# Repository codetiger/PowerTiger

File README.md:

# PowerTiger

## Overview
This project is an open-source energy monitoring solution designed to track and measure power consumption in a household. The design is centered around the Raspberry Pi Pico W, interfaced with Current Transformer (CT) sensors via a custom PCB. The project is developed using KiCad for PCB design and is part of an open-source hardware (OSH) initiative.

## Features
1. Real-time power monitoring: Accurately measure and track power usage in real-time using CT sensors.
2. Wireless communication: The RPi Pico W provides wireless connectivity, enabling easy integration with IoT platforms.
3. Scalable design: Supports multiple CT sensors to monitor different circuits or devices.
4. Open-source hardware and software: The design files and source code are freely available for customization and improvement as part of the OSH initiative.

## Project Components
* Raspberry Pi Pico W: The microcontroller at the heart of the project, providing processing power and wireless connectivity.
* Custom PCB: Designed in KiCad, this PCB interfaces with the CT sensors for power measurement of various terminals.
* CT Sensors: Used to measure the current flowing through the electrical wires, providing the data needed for power calculation.
* Software: The firmware is written in CircuitPython, running on the RPi Pico W.

| | Components | Count |
|-|------------|-------|
|1| SCT-013-030 | 5 |
|2| SCT-013-015 | 5 |
|3| SCT-013-005 | 6 |

The json config support configuring 16 CT sensors in any combination as required.

## Grafana Dashboard

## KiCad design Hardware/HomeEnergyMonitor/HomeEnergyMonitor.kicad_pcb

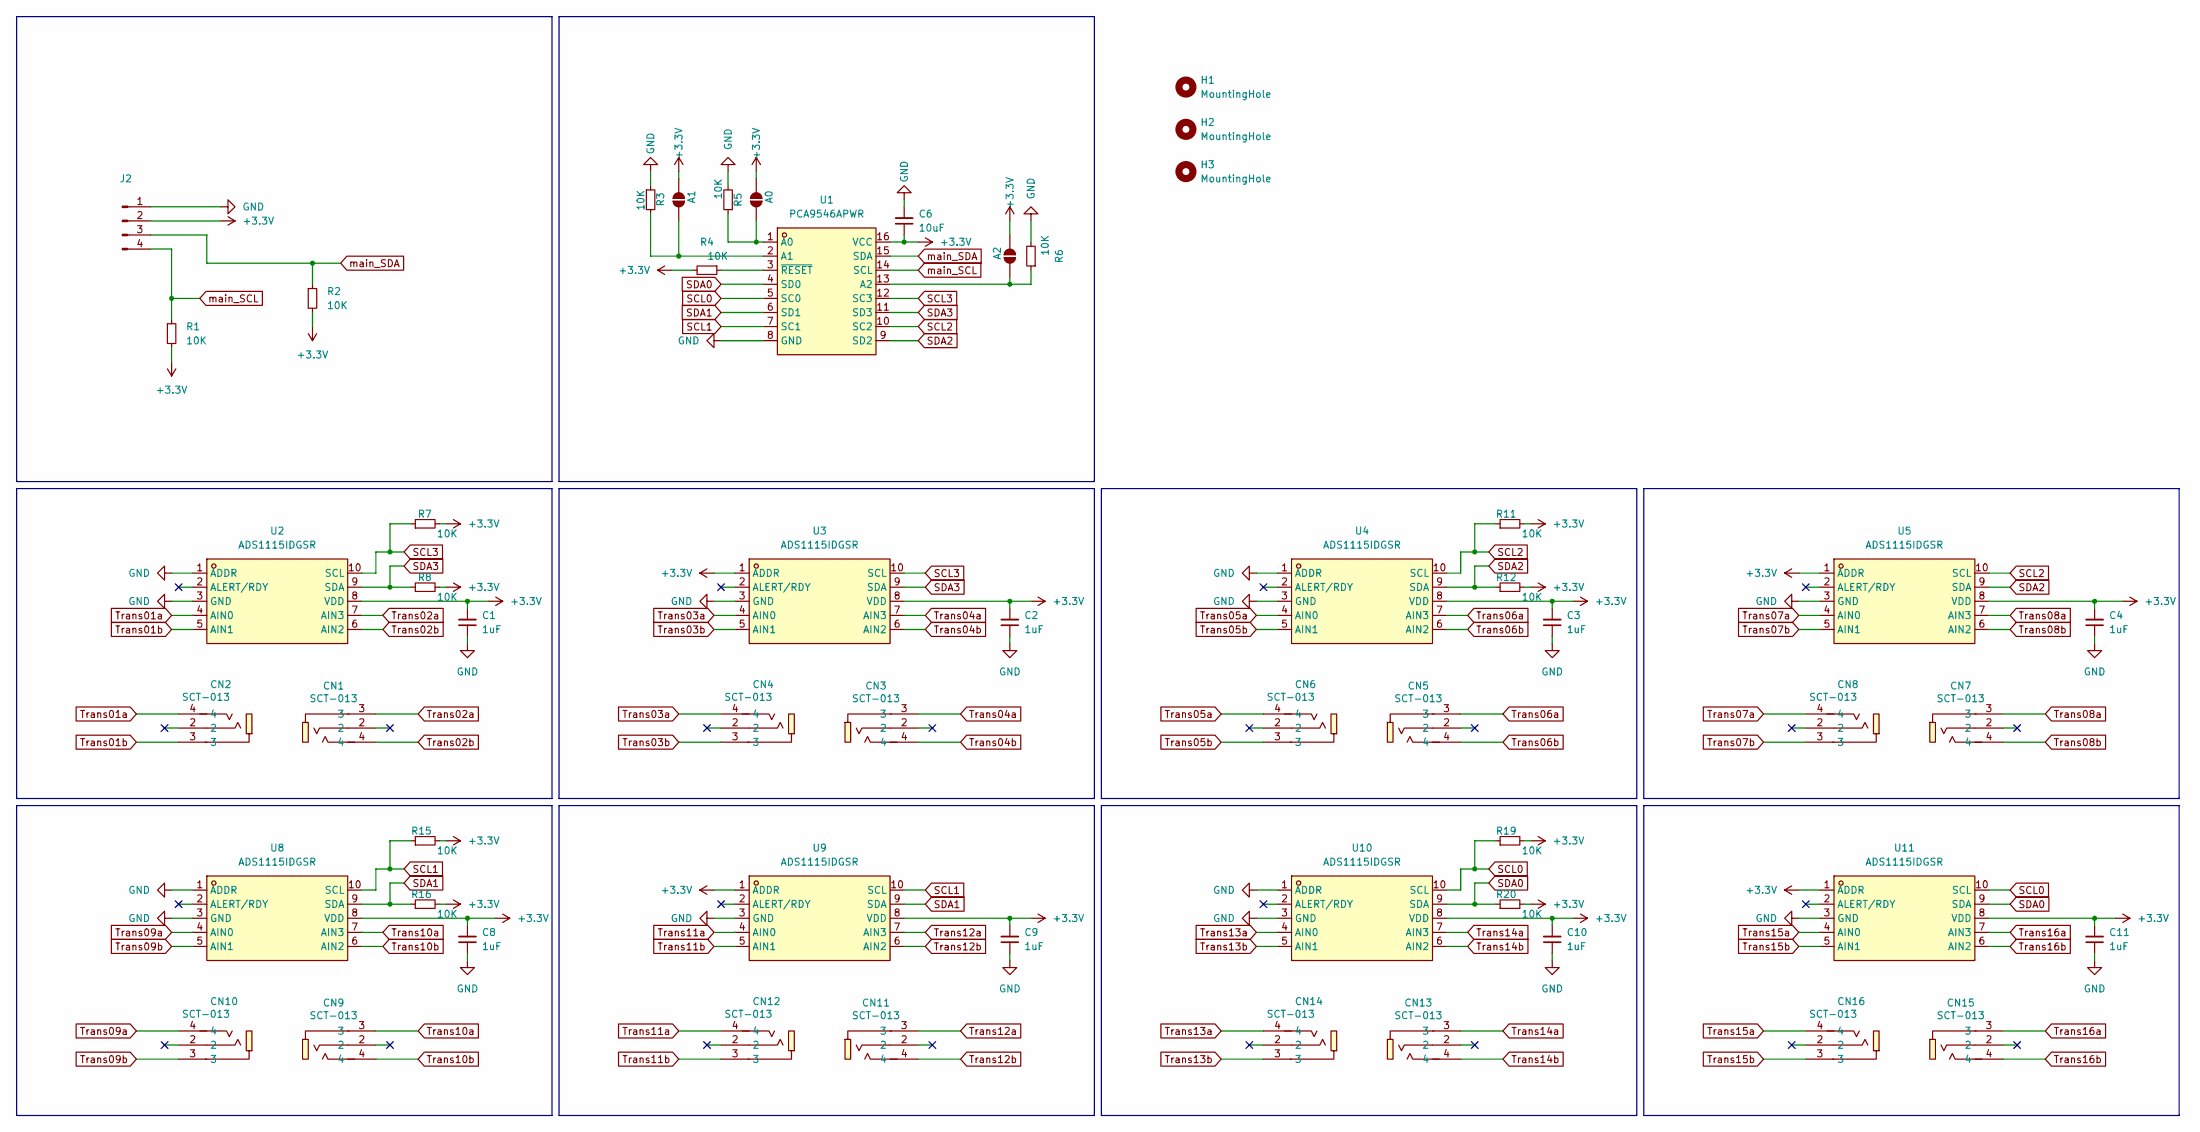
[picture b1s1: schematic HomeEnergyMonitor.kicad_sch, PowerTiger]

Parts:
A0, A1, A2: SolderJumper_2_Open; SolderJumper-2_P1.3mm_Open_RoundedPad1.0x1.5mm
C1, C2, C3, C4, C8, C9, C10, C11: 1uF; C_0603_1608Metric; Mfr. Part # CL10A105KO8NNNC; LCSC Part C1592
C6: 10uF; C_0603_1608Metric; Mfr. Part # CL10A106MP8NNNC; LCSC Part C85713
CN1, CN2, CN3, CN4, CN5, CN6, CN7, CN8, CN9, CN10, CN11, CN12, CN13, CN14, CN15, CN16: SCT-013; AUDIO-TH_PJ-3200; LCSC Part C2689690
H1, H2, H3: MountingHole; MountingHole_2.5mm
J2: Conn_01x04_Pin; PinHeader_1x04_P2.54mm_Vertical
R1, R2, R3, R4, R5, R6, R7, R8, R11, R12, R15, R16, R19, R20: 10K; R_0603_1608Metric; Mfr. Part # 0603WAF1002T5E; LCSC Part C25804
U1: PCA9546APWR; TSSOP-16_L5.0-W4.4-P0.65-LS6.4-BL; Mfr. Part # PCA9546APWR; LCSC Part C400705
U2, U3, U4, U5, U8, U9, U10, U11: ADS1115IDGSR; MSOP-10_L3.0-W3.0-P0.50-LS5.0-BL; Mfr. Part # ADS1115IDGSR; LCSC Part C37593

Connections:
+3.3V: A0.2 (B), A1.2 (B), A2.2 (B), C1.2, C2.2, C3.2, C4.2, C6.1, C8.2, C9.2, C10.2, C11.2, J2.2, R1.2, R2.2, R4.2, R7.2, R8.2, R11.2, R12.2, R15.2, R16.2, R19.2, R20.2, U1.16 (VCC), U2.8 (VDD), U3.1 (ADDR), U3.8 (VDD), U4.8 (VDD), U5.1 (ADDR), U5.8 (VDD), U8.8 (VDD), U9.1 (ADDR), U9.8 (VDD), U10.8 (VDD), U11.1 (ADDR), U11.8 (VDD)
GND: C1.1, C2.1, C3.1, C4.1, C6.2, C8.1, C9.1, C10.1, C11.1, J2.1, R3.1, R5.2, R6.2, U1.8 (GND), U2.1 (ADDR), U2.3 (GND), U3.3 (GND), U4.1 (ADDR), U4.3 (GND), U5.3 (GND), U8.1 (ADDR), U8.3 (GND), U9.3 (GND), U10.1 (ADDR), U10.3 (GND), U11.3 (GND)
unnamed: A0.1 (A), R5.1, U1.1 (A0)
unnamed: A1.1 (A), R3.2, U1.2 (A1)
unnamed: A2.1 (A), R6.1, U1.13 (A2)
unnamed: R4.1, U1.3 (~RESET)
SCL0: R19.1, U1.5 (SC0), U10.10 (SCL), U11.10 (SCL)
SCL1: R15.1, U1.7 (SC1), U8.10 (SCL), U9.10 (SCL)
SCL2: R11.1, U1.10 (SC2), U4.10 (SCL), U5.10 (SCL)
SCL3: R7.1, U1.12 (SC3), U2.10 (SCL), U3.10 (SCL)
SDA0: R20.1, U1.4 (SD0), U10.9 (SDA), U11.9 (SDA)
SDA1: R16.1, U1.6 (SD1), U8.9 (SDA), U9.9 (SDA)
SDA2: R12.1, U1.9 (SD2), U4.9 (SDA), U5.9 (SDA)
SDA3: R8.1, U1.11 (SD3), U2.9 (SDA), U3.9 (SDA)
Trans01a: CN2.4, U2.4 (AIN0)
Trans01b: CN2.3, U2.5 (AIN1)
Trans02a: CN1.3, U2.7 (AIN3)
Trans02b: CN1.4, U2.6 (AIN2)
Trans03a: CN4.4, U3.4 (AIN0)
Trans03b: CN4.3, U3.5 (AIN1)
Trans04a: CN3.3, U3.7 (AIN3)
Trans04b: CN3.4, U3.6 (AIN2)
Trans05a: CN6.4, U4.4 (AIN0)
Trans05b: CN6.3, U4.5 (AIN1)
Trans06a: CN5.3, U4.7 (AIN3)
Trans06b: CN5.4, U4.6 (AIN2)
Trans07a: CN8.4, U5.4 (AIN0)
Trans07b: CN8.3, U5.5 (AIN1)
Trans08a: CN7.3, U5.7 (AIN3)
Trans08b: CN7.4, U5.6 (AIN2)
Trans09a: CN10.4, U8.4 (AIN0)
Trans09b: CN10.3, U8.5 (AIN1)
Trans10a: CN9.3, U8.7 (AIN3)
Trans10b: CN9.4, U8.6 (AIN2)
Trans11a: CN12.4, U9.4 (AIN0)
Trans11b: CN12.3, U9.5 (AIN1)
Trans12a: CN11.3, U9.7 (AIN3)
Trans12b: CN11.4, U9.6 (AIN2)
Trans13a: CN14.4, U10.4 (AIN0)
Trans13b: CN14.3, U10.5 (AIN1)
Trans14a: CN13.3, U10.7 (AIN3)
Trans14b: CN13.4, U10.6 (AIN2)
Trans15a: CN16.4, U11.4 (AIN0)
Trans15b: CN16.3, U11.5 (AIN1)
Trans16a: CN15.3, U11.7 (AIN3)
Trans16b: CN15.4, U11.6 (AIN2)
main_SCL: J2.4, R1.1, U1.14 (SCL)
main_SDA: J2.3, R2.1, U1.15 (SDA)

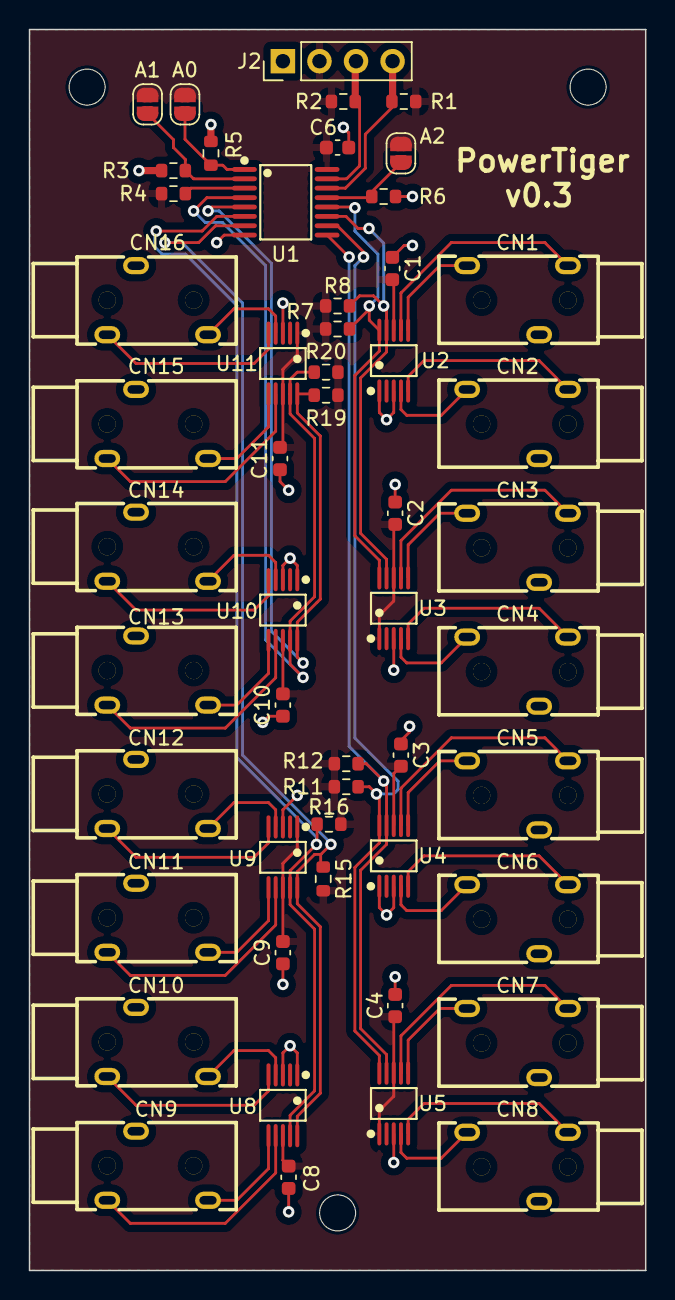
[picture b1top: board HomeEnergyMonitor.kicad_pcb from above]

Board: 2 copper layers, 42.8 x 86.2 mm, 55 parts (0 on the bottom side), 48 nets.

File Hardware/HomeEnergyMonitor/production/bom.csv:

Designator,Footprint,Quantity,Value,LCSC Part #
"C1, C10, C11, C2, C3, C4, C8, C9",0603,8,1uF,C1592
C6,0603,1,10uF,C85713
"CN1, CN10, CN11, CN12, CN13, CN14, CN15, CN16, CN2, CN3, CN4, CN5, CN6, CN7, CN8, CN9",AUDIO-TH_PJ-3200,16,SCT-013,C2689690
J2,PinHeader_1x04_P2.54mm_Vertical,1,Conn_01x04_Pin,
"R1, R11, R12, R15, R16, R19, R2, R20, R3, R4, R5, R6, R7, R8",0603,14,10K,C23162
U1,TSSOP-16_L5.0-W4.4-P0.65-LS6.4-BL,1,PCA9546APWR,C400705
"U10, U11, U2, U3, U4, U5, U8, U9",MSOP-10_L3.0-W3.0-P0.50-LS5.0-BL,8,ADS1115IDGSR,C37593

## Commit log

2024-08-02 Working PCB and CircuitPython application for Prometheus exporter
2024-08-16 Completed working version hw, sw and case
2024-08-21 Externalise device config for easy of config
2024-08-24 Added Grafana Dashboard
2024-08-24 Added more details about the project in Readme file.
2024-08-24 Added Logo for PowerTiger
